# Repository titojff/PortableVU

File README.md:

# PortableVU

This can be used in a Disco club etc.

It's powered by 4 AA batteries

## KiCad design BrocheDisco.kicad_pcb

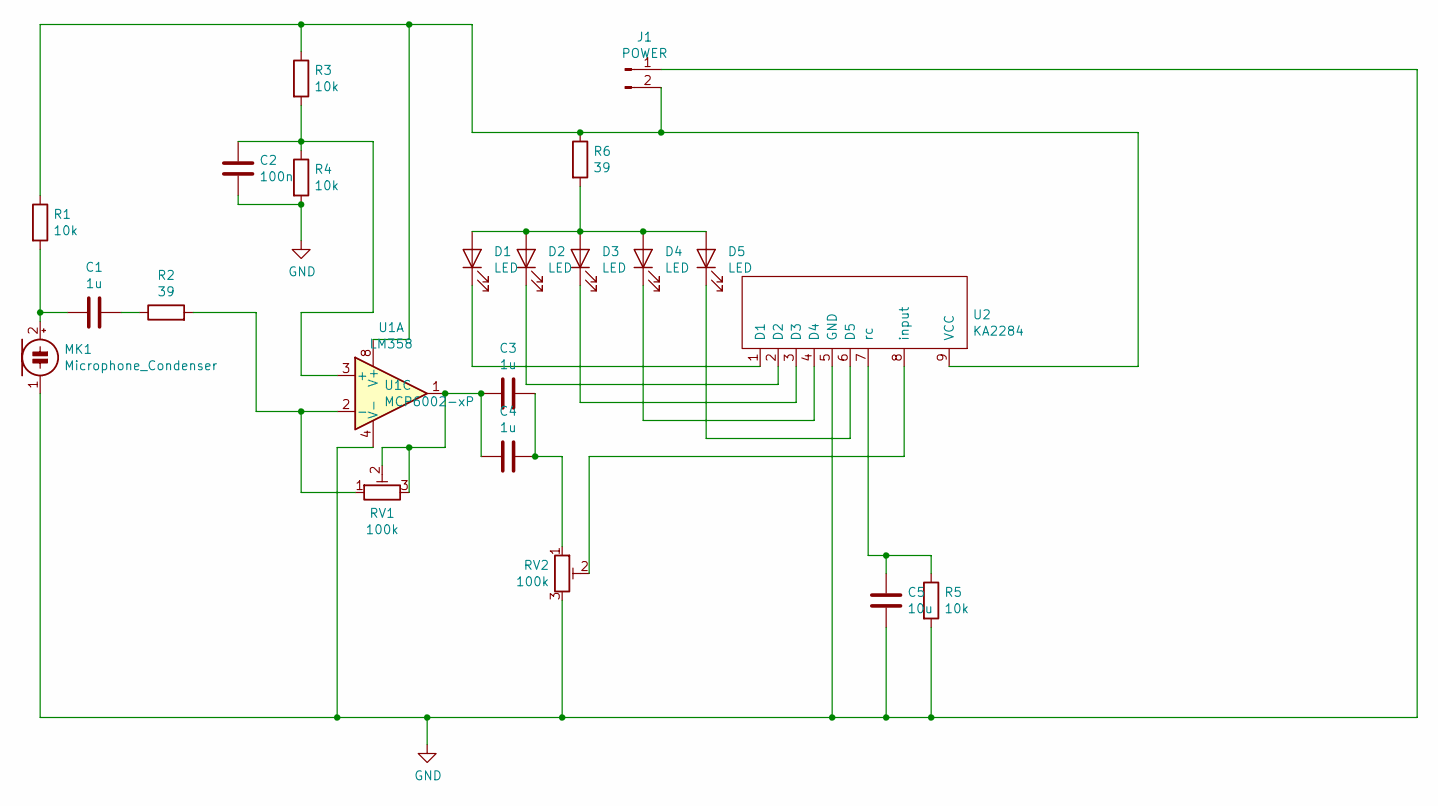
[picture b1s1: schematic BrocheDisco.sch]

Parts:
C1, C3, C4: 1u; CP_Radial_D5.0mm_P2.00mm
C2: 100n; C_Disc_D8.0mm_W5.0mm_P5.00mm
C5: 10u; CP_Radial_D10.0mm_P3.50mm
D1, D2, D3, D4, D5: LED; LED_D3.0mm_FlatTop
J1: POWER; SolderWirePad_1x02_P3.81mm_Drill0.8mm
MK1: Microphone_Condenser; PinHeader_1x02_P2.00mm_Horizontal
R1, R3, R4, R5: 10k; R_Axial_DIN0204_L3.6mm_D1.6mm_P7.62mm_Horizontal
R2, R6: 39; R_Axial_DIN0414_L11.9mm_D4.5mm_P20.32mm_Horizontal
RV1, RV2: 100k; Potentiometer_ACP_CA9-H2,5_Horizontal
U1: LM358; DIP-8_W7.62mm_LongPads
U2: KA2284; SIP9_Housing_BigPads

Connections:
GND: C2.2, C5.2, J1.1, MK1.1 (-), R4.2, R5.2, RV2.3, U1.4 (V-), U2.5 (GND)
unnamed: C1.1, R2.1
unnamed: C1.2, MK1.2 (+), R1.2
unnamed: C2.1, R3.2, R4.1, U1.3 (+)
unnamed: C3.1, C4.1, RV2.1
unnamed: C3.2, C4.2, RV1.2, RV1.3, U1.1
unnamed: C5.1, R5.1, U2.7 (rc)
unnamed: D1.1 (K), U2.1 (D1)
unnamed: D1.2 (A), D2.2 (A), D3.2 (A), D4.2 (A), D5.2 (A), R6.2
unnamed: D2.1 (K), U2.2 (D2)
unnamed: D3.1 (K), U2.3 (D3)
unnamed: D4.1 (K), U2.4 (D4)
unnamed: D5.1 (K), U2.6 (D5)
unnamed: J1.2, R1.1, R3.1, R6.1, U1.8 (V+), U2.9 (VCC)
unnamed: R2.2, RV1.1, U1.2 (-)
unnamed: RV2.2, U2.8 (input)

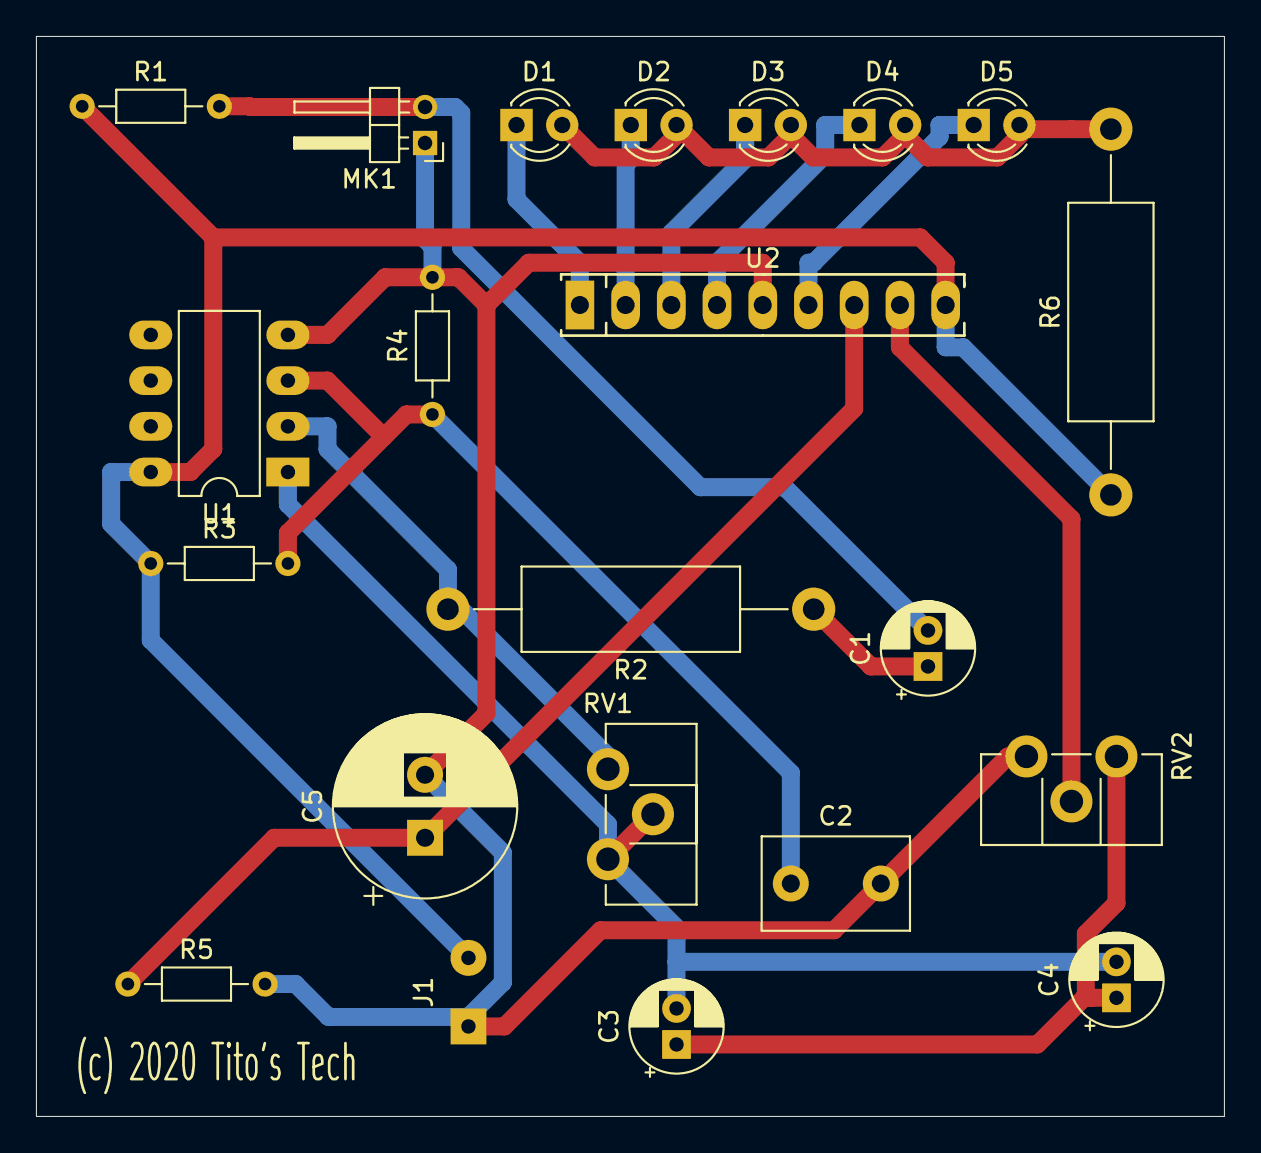
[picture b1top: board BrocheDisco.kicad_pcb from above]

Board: 2 copper layers, 66.0 x 60.0 mm, 22 parts (0 on the bottom side), 16 nets.

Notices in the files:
BrocheDisco.kicad_pcb:
(c) 2020 Tito's Tech
